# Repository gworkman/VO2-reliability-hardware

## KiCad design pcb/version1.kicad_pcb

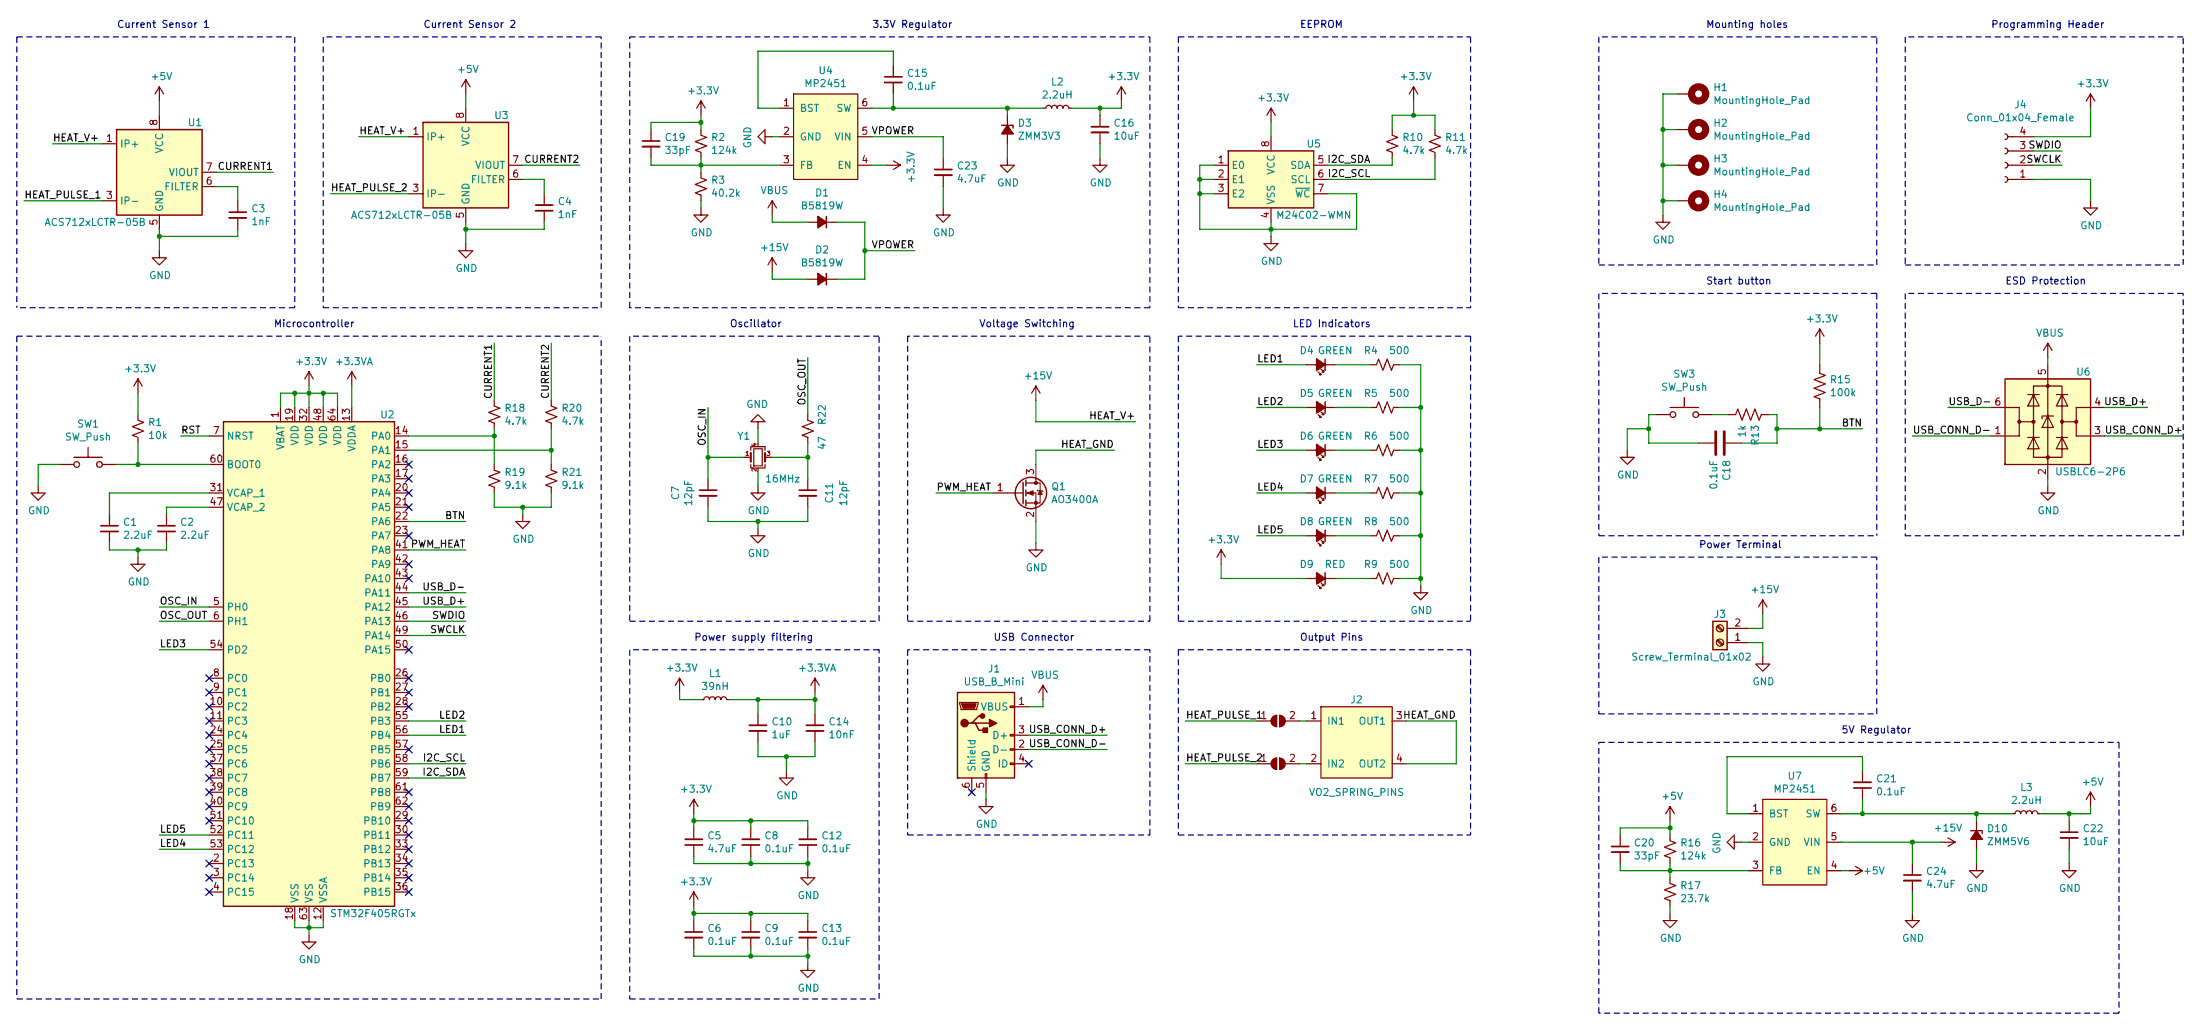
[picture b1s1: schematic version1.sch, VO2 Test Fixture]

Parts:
C1, C2: 2.2uF; C_0603_1608Metric
C3, C4: 1nF; C_0603_1608Metric
C5, C23, C24: 4.7uF; C_0603_1608Metric
C6, C8, C9, C12, C13, C15, C18, C21: 0.1uF; C_0603_1608Metric
C7, C11: 12pF; C_0603_1608Metric
C10: 1uF; C_0603_1608Metric
C14: 10nF; C_0603_1608Metric
C16, C22: 10uF; C_0603_1608Metric
C19, C20: 33pF; C_0603_1608Metric
D1, D2: B5819W; D_SOD-123
D3: ZMM3V3; D_MiniMELF
D4, D5, D6, D7, D8: GREEN; LED_0805_2012Metric
D9: RED; LED_0805_2012Metric
D10: ZMM5V6; D_MiniMELF
H1, H2, H3, H4: MountingHole_Pad; MountingHole_2.2mm_M2_Pad_Via
J1: USB_B_Mini; USB_Mini-B_Wuerth_65100516121_Horizontal
J2: VO2_SPRING_PINS; SPRING_PINS
J3: Screw_Terminal_01x02; TerminalBlock_MetzConnect_Type055_RT01502HDWU_1x02_P5.00mm_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
J4: Conn_01x04_Female; PinSocket_1x04_P2.54mm_Vertical
JP2, JP3: Solder Bridge; SolderJumper-2_P1.3mm_Open_RoundedPad1.0x1.5mm
L1: 39nH; L_0402_1005Metric
L2, L3: 2.2uH; L_0805_2012Metric
Q1: AO3400A; SOT-23
R1: 10k; R_0603_1608Metric
R2, R16: 124k; R_0603_1608Metric
R3: 40.2k; R_0603_1608Metric
R4, R5, R6, R7, R8, R9: 500; R_0603_1608Metric
R10, R11, R18, R20: 4.7k; R_0603_1608Metric
R13: 1k; R_0603_1608Metric
R15: 100k; R_0603_1608Metric
R17: 23.7k; R_0603_1608Metric
R19, R21: 9.1k; R_0603_1608Metric
R22: 47; R_0603_1608Metric
SW1, SW3: SW_Push; SW_PUSH_6mm
U1, U3: ACS712xLCTR-05B; SOIC-8_3.9x4.9mm_P1.27mm
U2: STM32F405RGTx; LQFP-64_10x10mm_P0.5mm
U4, U7: MP2451; SOT-23-6
U5: M24C02-WMN; SOIC-8_3.9x4.9mm_P1.27mm
U6: USBLC6-2P6; SOT-666
Y1: 16MHz; Crystal_SMD_SeikoEpson_FA238-4Pin_3.2x2.5mm

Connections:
+3.3VA: C10.1, C14.1, L1.2, U2.13 (VDDA)
+3V3: C5.1, C6.1, C8.1, C9.1, C12.1, C13.1, C16.1, C19.1, D9.2 (A), J4.4, L1.1, L2.2, R1.1, R2.2, R10.1, R11.2, R15.1, U2.1 (VBAT), U2.19 (VDD), U2.32 (VDD), U2.48 (VDD), U2.64 (VDD), U4.4 (EN), U5.8 (VCC)
+5V: C20.1, C22.1, L3.2, R16.2, U1.8 (VCC), U3.8 (VCC), U7.4 (EN)
+15V: C24.1, D2.2 (A), J3.2, U1.1 (IP+), U1.2 (IP+), U3.1 (IP+), U3.2 (IP+), U7.5 (VIN)
/BTN: C18.1, R13.1, R15.2, U2.22 (PA6)
/CURRENT1: R18.2, U1.7 (VIOUT)
/CURRENT2: R20.2, U3.7 (VIOUT)
/HEAT_GND: J2.3 (OUT1), J2.4 (OUT2), Q1.3 (D)
/HEAT_PULSE_1: JP2.1 (A), U1.3 (IP-), U1.4 (IP-)
/HEAT_PULSE_2: JP3.1 (A), U3.3 (IP-), U3.4 (IP-)
/I2C_SCL: R11.1, U2.58 (PB6), U5.6 (SCL)
/I2C_SDA: R10.2, U2.59 (PB7), U5.5 (SDA)
/LED1: D4.2 (A), U2.56 (PB4)
/LED2: D5.2 (A), U2.55 (PB3)
/LED3: D6.2 (A), U2.54 (PD2)
/LED4: D7.2 (A), U2.53 (PC12)
/LED5: D8.2 (A), U2.52 (PC11)
/OSC_IN: C7.1, U2.5 (PH0), Y1.1
/OSC_OUT: R22.2, U2.6 (PH1)
/PWM_HEAT: Q1.1 (G), U2.41 (PA8)
/RST: U2.7 (NRST)
/SWCLK: J4.2, U2.49 (PA14)
/SWDIO: J4.3, U2.46 (PA13)
/USB_CONN_D+: J1.3 (D+), U6.3 (I/O2)
/USB_CONN_D-: J1.2 (D-), U6.1 (I/O1)
/USB_D+: U2.45 (PA12), U6.4 (I/O2)
/USB_D-: U2.44 (PA11), U6.6 (I/O1)
/VPOWER: C23.1, D1.1 (K), D2.1 (K), U4.5 (VIN)
GND: C1.2, C2.2, C3.2, C4.2, C5.2, C6.2, C7.2, C8.2, C9.2, C10.2, C11.2, C12.2, C13.2, C14.2, C16.2, C18.2, C22.2, C23.2, C24.2, D3.2 (A), D10.2 (A), H1.1, H2.1, H3.1, H4.1, J1.5 (GND), J3.1, J4.1, Q1.2 (S), R3.1, R4.1, R5.1, R6.1, R7.1, R8.1, R9.1, R17.1, R19.1, R21.1, SW1.1, SW3.1, U1.5 (GND), U2.12 (VSSA), U2.18 (VSS), U2.63 (VSS), U3.5 (GND), U4.2 (GND), U5.1 (E0), U5.2 (E1), U5.3 (E2), U5.4 (VSS), U5.7 (~WC), U6.2 (GND), U7.2 (GND), Y1.2, Y1.4
unnamed: C1.1, U2.31 (VCAP_1)
unnamed: C2.1, U2.47 (VCAP_2)
unnamed: C3.1, U1.6 (FILTER)
unnamed: C4.1, U3.6 (FILTER)
unnamed: C11.1, R22.1, Y1.3
unnamed: C15.1, U4.1 (BST)
unnamed: C15.2, D3.1 (K), L2.1, U4.6 (SW)
unnamed: C19.2, R2.1, R3.2, U4.3 (FB)
unnamed: C20.2, R16.1, R17.2, U7.3 (FB)
unnamed: C21.1, U7.1 (BST)
unnamed: C21.2, D10.1 (K), L3.1, U7.6 (SW)
unnamed: D4.1 (K), R4.2
unnamed: D5.1 (K), R5.2
unnamed: D6.1 (K), R6.2
unnamed: D7.1 (K), R7.2
unnamed: D8.1 (K), R8.2
unnamed: D9.1 (K), R9.2
unnamed: J2.1 (IN1), JP2.2 (B)
unnamed: J2.2 (IN2), JP3.2 (B)
unnamed: R1.2, SW1.2, U2.60 (BOOT0)
unnamed: R13.2, SW3.2
unnamed: R18.1, R19.2, U2.14 (PA0)
unnamed: R20.1, R21.2, U2.15 (PA1)
VBUS: D1.2 (A), J1.1 (VBUS), U6.5 (VBUS)

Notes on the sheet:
3.3V Regulator
Start button
Microcontroller
Programming Header
LED Indicators
Output Pins
Current Sensor 1
Current Sensor 2
Power supply filtering
Oscillator
Voltage Switching
USB Connector
EEPROM
ESD Protection
Power Terminal
5V Regulator
Mounting holes

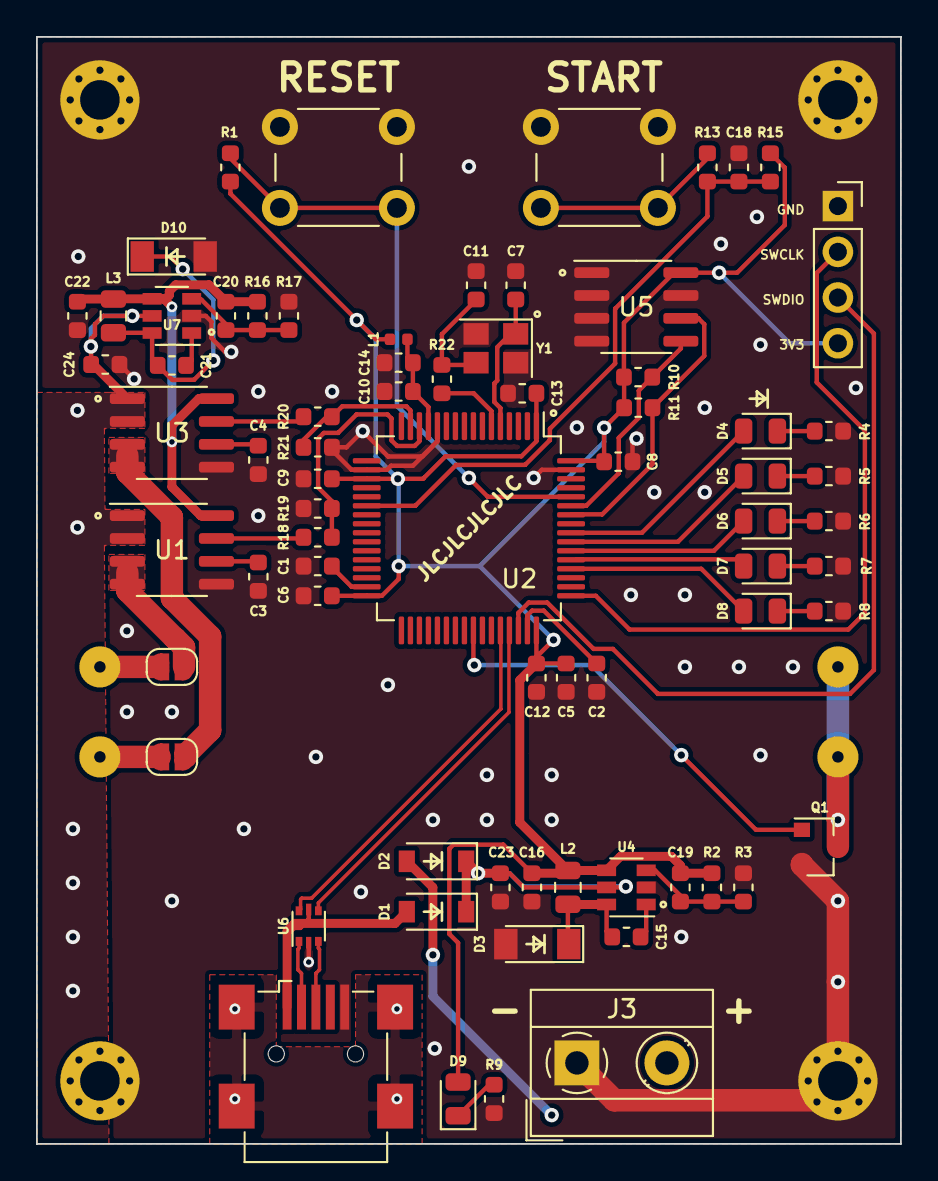
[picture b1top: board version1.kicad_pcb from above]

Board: 2 copper layers, 48.0 x 61.5 mm, 77 parts (0 on the bottom side), 52 nets.

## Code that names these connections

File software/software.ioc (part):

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Mcu.UserName=STM32G030K6Tx
PA14-BOOT0.Mode=Serial_Wire
PA0.GPIO_Label=BTN
PA3.GPIOParameters=GPIO_Label
PB6.GPIO_Label=LED4
PA2.GPIOParameters=GPIO_Label
PB5.GPIOParameters=GPIO_Label
PB4.GPIOParameters=GPIO_Label
PA4.Mode=IN4
PB6.Signal=GPIO_Output
PA14-BOOT0.Signal=SYS_SWCLK
RCC.HSE_VALUE=8000000
PB3.GPIOParameters=GPIO_Label
PB7.Signal=GPIO_Output
PB6.GPIOParameters=GPIO_Label
PA0.Signal=GPIO_Input
PB7.GPIO_Label=LED5
Mcu.Package=LQFP32
PA2.GPIO_Label=ADC_16V
PA10.Signal=USART1_RX
PB5.GPIO_Label=LED3
PA4.GPIO_Label=ADC_HEAT2
PB4.Signal=GPIO_Output
PA3.Signal=ADC1_IN3
PB3.GPIO_Label=LED1
PA10.Mode=Asynchronous
PC6.Signal=S_TIM3_CH1
PA13.Signal=SYS_SWDIO
PA3.Mode=IN3
PA9.Mode=Asynchronous
PB7.GPIOParameters=GPIO_Label
PA9.Signal=USART1_TX
board=custom
PB4.GPIO_Label=LED2
PA4.GPIOParameters=GPIO_Label
PA13.Mode=Serial_Wire
Mcu.Name=STM32G030K(6-8)Tx
PA2.Signal=ADC1_IN2
PB3.Signal=GPIO_Output
PA4.Signal=ADC1_IN4
RCC.SYSCLKFreq_VALUE=16000000
PB5.Signal=GPIO_Output
PA0.GPIOParameters=GPIO_Label
PA2.Mode=IN2
PA3.GPIO_Label=ADC_HEAT1

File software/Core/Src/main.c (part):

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volatile uint16_t adc_buf[ADC_BUF_LEN];
volatile uint8_t uart_buf[5];
volatile float source_voltage = 0;
volatile float current1 = 0;
volatile float current2 = 0;
volatile bool running = false;
volatile bool stream_adc = false;
volatile uint32_t cycle_count = 0;
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      memcpy(&update_packets[VOLTAGE].data, &source_voltage, sizeof(source_voltage));
      memcpy(&update_packets[CURRENT1].data, &current1, sizeof(current1));
      memcpy(&update_packets[CURRENT2].data, &current2, sizeof(current2));
      update_packets[BUTTON].data[0] = HAL_GPIO_ReadPin(BTN_GPIO_Port, BTN_Pin) == GPIO_PIN_RESET;
      memcpy(&update_packets[MICROS_ON].data, &on_time, sizeof(uint32_t));
      memcpy(&update_packets[MICROS_OFF].data, &off_time, sizeof(uint32_t));

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  __HAL_RCC_GPIOB_CLK_ENABLE();

  /*Configure GPIO pin Output Level */
  HAL_GPIO_WritePin(GPIOB, LED1_Pin | LED2_Pin | LED3_Pin | LED4_Pin | LED5_Pin, GPIO_PIN_RESET);

  /*Configure GPIO pin : BTN_Pin */
  GPIO_InitStruct.Pin = BTN_Pin;
  GPIO_InitStruct.Mode = GPIO_MODE_INPUT;
  GPIO_InitStruct.Pull = GPIO_NOPULL;
  HAL_GPIO_Init(BTN_GPIO_Port, &GPIO_InitStruct);

  /*Configure GPIO pins : LED1_Pin LED2_Pin LED3_Pin LED4_Pin
                           LED5_Pin */
  GPIO_InitStruct.Pin = LED1_Pin | LED2_Pin | LED3_Pin | LED4_Pin | LED5_Pin;
  GPIO_InitStruct.Mode = GPIO_MODE_OUTPUT_PP;
  GPIO_InitStruct.Pull = GPIO_NOPULL;
  GPIO_InitStruct.Speed = GPIO_SPEED_FREQ_LOW;
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/* USER CODE BEGIN 4 */
void HAL_ADC_ConvCpltCallback(ADC_HandleTypeDef *hadc)
{
  // HAL_GPIO_TogglePin(LED1_GPIO_Port, LED1_Pin);
  HAL_ADC_Start_DMA(&hadc1, (uint32_t *)adc_buf, ADC_BUF_LEN);
}

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  {
    HAL_TIM_PWM_Stop_IT(&htim3, TIM_CHANNEL_1);
    running = false;
    HAL_GPIO_WritePin(LED5_GPIO_Port, LED5_Pin, GPIO_PIN_SET);
  }

  uint16_t leds_on = 0;
  leds_on |= cycle_count >= led_on_values[0] ? LED1_Pin : 0;
  leds_on |= cycle_count >= led_on_values[1] ? LED2_Pin : 0;
  leds_on |= cycle_count >= led_on_values[2] ? LED3_Pin : 0;
  leds_on |= cycle_count >= led_on_values[3] ? LED4_Pin : 0;
  HAL_GPIO_WritePin(LED1_GPIO_Port, leds_on, GPIO_PIN_SET);
}

void HAL_UART_RxCpltCallback(UART_HandleTypeDef *huart)
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    {
      cycle_count = 0;
      HAL_TIM_PWM_Start_IT(&htim3, TIM_CHANNEL_1);
      HAL_GPIO_WritePin(LED1_GPIO_Port, LED1_Pin | LED2_Pin | LED3_Pin | LED4_Pin | LED5_Pin, GPIO_PIN_RESET);
    }
    else
    {
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
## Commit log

2020-11-12 updated hardware design
2020-11-12 add microcontroller firmware
2020-11-13 fix adc
2020-11-13 fix micros_on micros_off
2020-11-28 wip: add adc stream mode
2020-12-09 split repo into hardware only
2021-02-11 updated hardware

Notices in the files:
software/Core/Src/main.c:
© Copyright (c) 2020 STMicroelectronics.
All rights reserved.
This software component is licensed by ST under BSD 3-Clause license,
the "License"; You may not use this file except in compliance with the
License. You may obtain a copy of the License at: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
(C) COPYRIGHT STMicroelectronics *****END OF FILE
